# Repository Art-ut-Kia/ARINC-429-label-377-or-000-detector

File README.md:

# ARINC-429-label-377-or-000-detector
Electronic Circuit designed with Cadsoft Eagle.
When connected to an ARINC 429 bus, generates a pulse when a word with the octal label 377 is detected.

Have a look to the [Wiki](https://github.com/Art-ut-Kia/ARINC-429-label-377-or-000-detector/wiki) for detailed description and simulation report.

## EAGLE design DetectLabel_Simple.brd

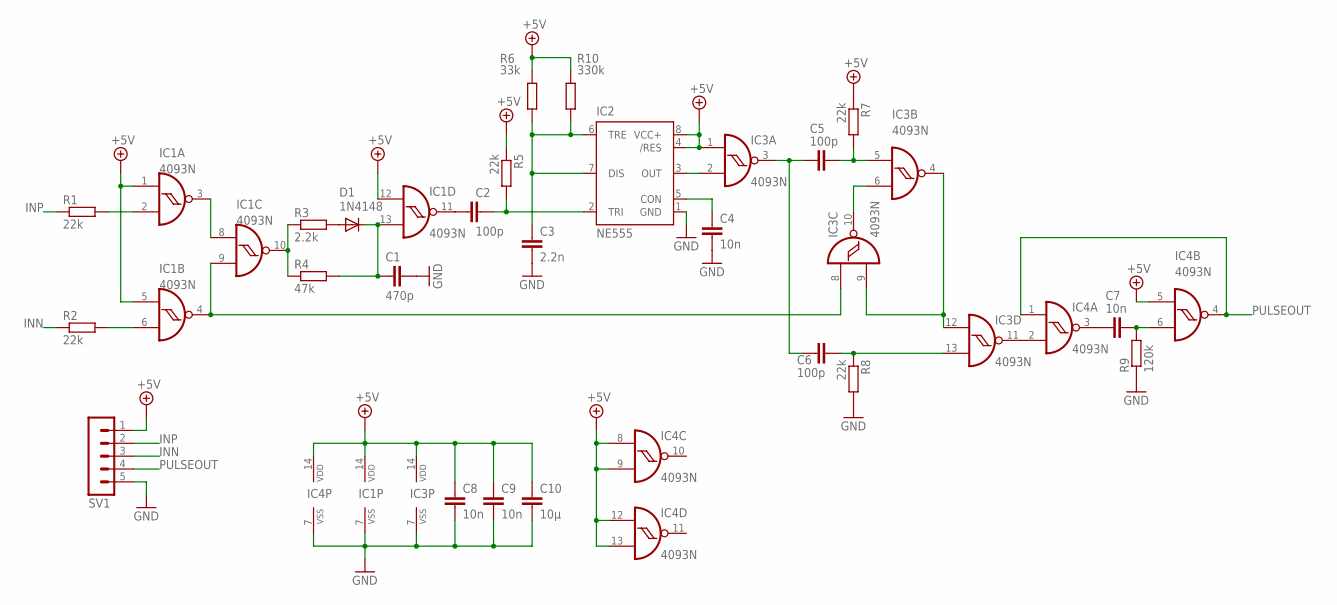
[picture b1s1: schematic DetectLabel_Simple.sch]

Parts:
C1: 470p; C050-025X075
C2, C5, C6: 100p; C050-025X075
C3: 2.2n; C050-025X075
C4, C7, C8, C9: 10n; C050-025X075
C10: 10µ; C050-025X075
D1: 1N4148; DO35-7
IC1, IC3, IC4: 4093N; DIL14
IC2: NE555; DIL-08
R1, R2, R5, R7, R8: 22k; 0309/10
R3: 2.2k; 0309/10
R4: 47k; 0309/10
R6: 33k; 0309/10
R9: 120k; 0309/10
R10: 330k; 0309/10
SV1: MA05-1

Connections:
+5V: C8.1, C9.1, C10.1, IC1.1 (I0), IC1.5 (I0), IC1.12 (I0), IC1.14 (VDD), IC2.4 (/RES), IC2.8 (VCC+), IC3.1 (I0), IC3.14 (VDD), IC4.5 (I0), IC4.8 (I0), IC4.9 (I1), IC4.12 (I0), IC4.13 (I1), IC4.14 (VDD), R5.1, R6.1, R7.1, R10.1, SV1.1
GND: C1.2, C3.2, C4.2, C8.2, C9.2, C10.2, IC1.7 (VSS), IC2.1 (GND), IC3.7 (VSS), IC4.7 (VSS), R8.2, R9.1, SV1.5
INN: R2.1, SV1.3
INP: R1.1, SV1.2
unnamed: IC1.2 (I1), R1.2
unnamed: IC1.6 (I1), R2.2
unnamed: IC1.10 (O), R3.1, R4.1
unnamed: IC1.3 (O), IC1.8 (I0)
unnamed: IC1.4 (O), IC1.9 (I1), IC3.8 (I0)
unnamed: D1.A, R3.2
unnamed: C1.1, D1.C, IC1.13 (I1), R4.2
unnamed: C2.1, IC1.11 (O)
unnamed: C2.2, IC2.2 (TRI), R5.2
unnamed: C7.1, IC4.3 (O)
unnamed: C3.1, IC2.6 (TRE), IC2.7 (DIS), R6.2, R10.2
unnamed: C4.1, IC2.5 (CON)
unnamed: IC2.3 (OUT), IC3.2 (I1)
unnamed: C5.1, C6.1, IC3.3 (O)
unnamed: C5.2, IC3.5 (I0), R7.2
unnamed: IC3.6 (I1), IC3.10 (O)
unnamed: IC3.4 (O), IC3.9 (I1), IC3.12 (I0)
unnamed: C6.2, IC3.13 (I1), R8.1
unnamed: IC3.11 (O), IC4.2 (I1)
unnamed: C7.2, IC4.6 (I1), R9.2
PULSEOUT: IC4.1 (I0), IC4.4 (O), SV1.4

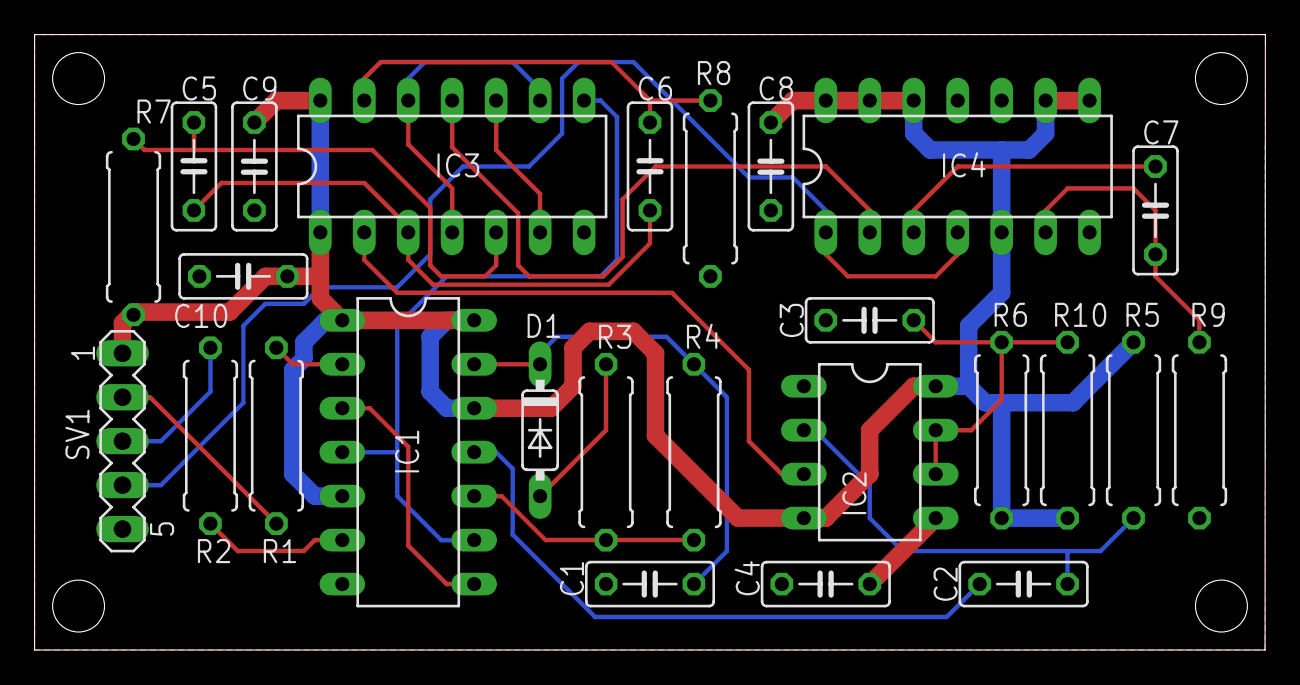
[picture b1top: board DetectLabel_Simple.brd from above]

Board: 2 copper layers, 71.1 x 35.6 mm, 26 parts (0 on the bottom side), 25 nets.

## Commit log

2016-05-06 New project
2016-05-06 Add Cadsoft Eagle files (SCHematics + BoaRD)
2016-05-06 directory for pictures illustrating the Wiki
2016-05-06 Eagle PCB screen shot
2016-05-07 A429 receiver and bit clock recovery chronograms
2016-05-07 word clock recovery
2016-05-07 Label Mask Generator
2016-05-07 flip flop
2016-05-07 output pulse generation
2020-01-24 Update README.md
    link to wiki
